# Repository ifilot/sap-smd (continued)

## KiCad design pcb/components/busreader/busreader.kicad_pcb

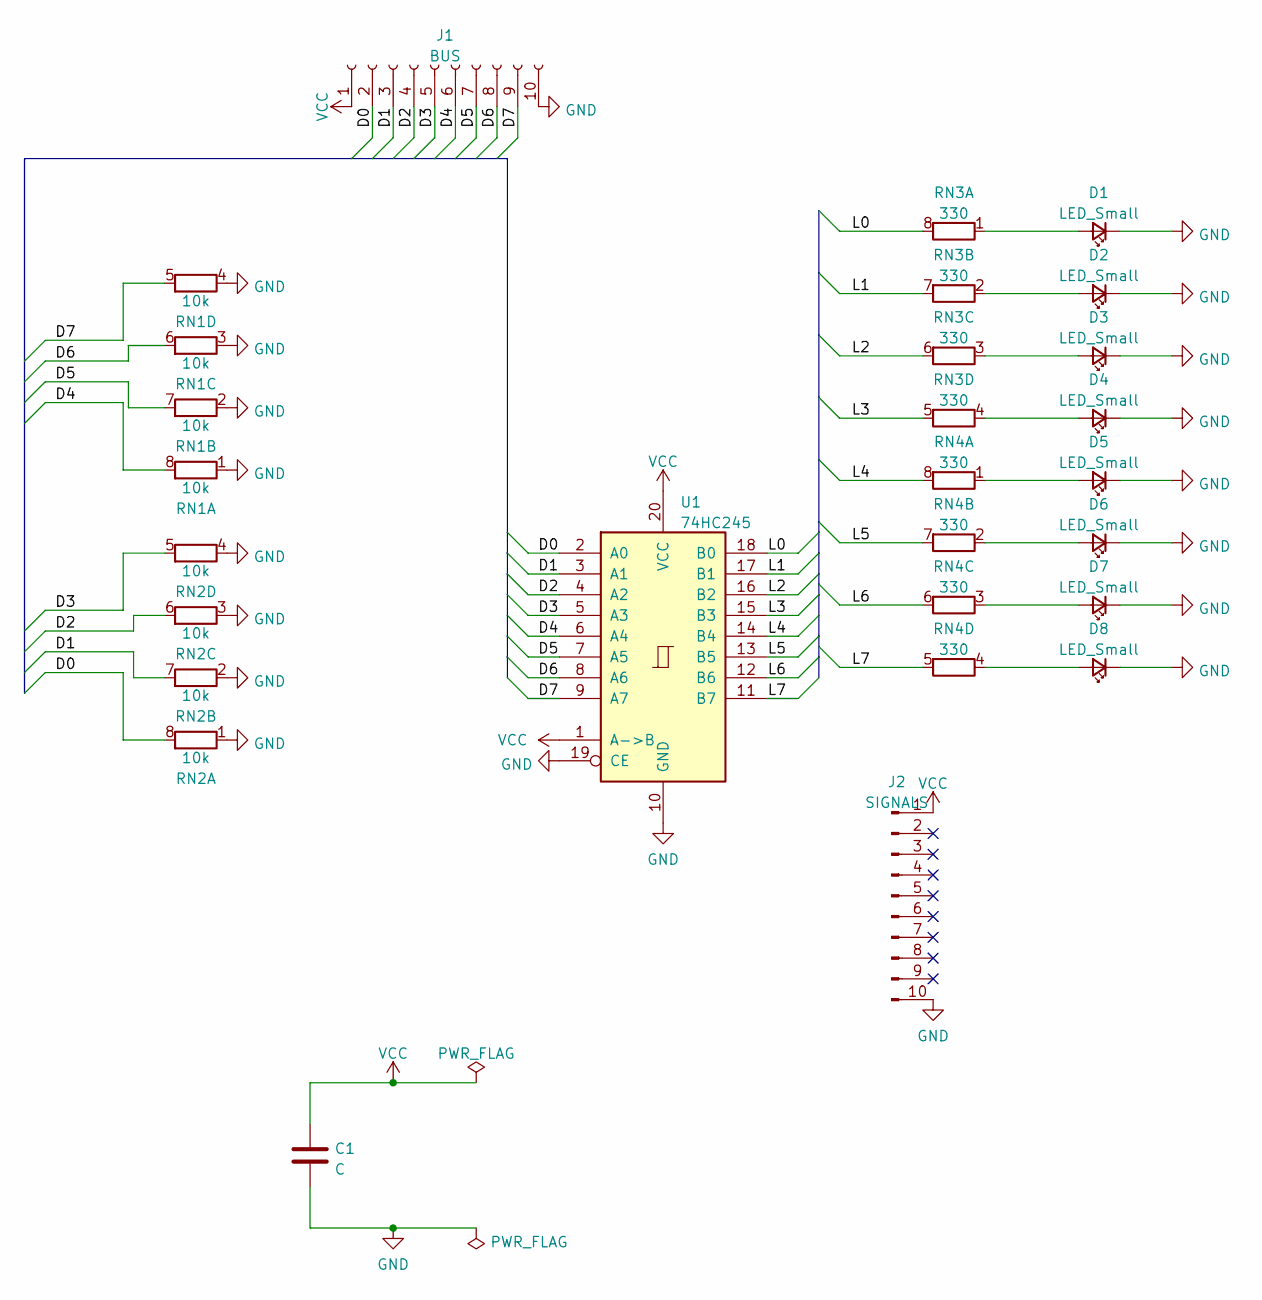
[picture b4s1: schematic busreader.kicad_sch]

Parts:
C1: C; C_0805_2012Metric
D1, D2, D3, D4, D5, D6, D7, D8: LED_Small; LED_0805_2012Metric
J1: BUS; PinHeader_1x10_P2.54mm_Vertical
J2: SIGNALS; PinHeader_1x10_P2.54mm_Vertical
RN1, RN2: 10k; R_Array_Convex_4x0603
RN3, RN4: 330; R_Array_Convex_4x0603
U1: 74HC245; SOIC-20W_7.5x12.8mm_P1.27mm

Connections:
/D0: J1.2, RN2.8 (R1.2), U1.2 (A0)
/D1: J1.3, RN2.7 (R2.2), U1.3 (A1)
/D2: J1.4, RN2.6 (R3.2), U1.4 (A2)
/D3: J1.5, RN2.5 (R4.2), U1.5 (A3)
/D4: J1.6, RN1.8 (R1.2), U1.6 (A4)
/D5: J1.7, RN1.7 (R2.2), U1.7 (A5)
/D6: J1.8, RN1.6 (R3.2), U1.8 (A6)
/D7: J1.9, RN1.5 (R4.2), U1.9 (A7)
/L0: RN3.8 (R1.2), U1.18 (B0)
/L1: RN3.7 (R2.2), U1.17 (B1)
/L2: RN3.6 (R3.2), U1.16 (B2)
/L3: RN3.5 (R4.2), U1.15 (B3)
/L4: RN4.8 (R1.2), U1.14 (B4)
/L5: RN4.7 (R2.2), U1.13 (B5)
/L6: RN4.6 (R3.2), U1.12 (B6)
/L7: RN4.5 (R4.2), U1.11 (B7)
GND: C1.2, D1.1 (K), D2.1 (K), D3.1 (K), D4.1 (K), D5.1 (K), D6.1 (K), D7.1 (K), D8.1 (K), J1.10, J2.10, RN1.1 (R1.1), RN1.2 (R2.1), RN1.3 (R3.1), RN1.4 (R4.1), RN2.1 (R1.1), RN2.2 (R2.1), RN2.3 (R3.1), RN2.4 (R4.1), U1.10 (GND), U1.19 (CE)
unnamed: D1.2 (A), RN3.1 (R1.1)
unnamed: D2.2 (A), RN3.2 (R2.1)
unnamed: D3.2 (A), RN3.3 (R3.1)
unnamed: D4.2 (A), RN3.4 (R4.1)
unnamed: D5.2 (A), RN4.1 (R1.1)
unnamed: D6.2 (A), RN4.2 (R2.1)
unnamed: D7.2 (A), RN4.3 (R3.1)
unnamed: D8.2 (A), RN4.4 (R4.1)
VCC: C1.1, J1.1, J2.1, U1.1 (A->B), U1.20 (VCC)

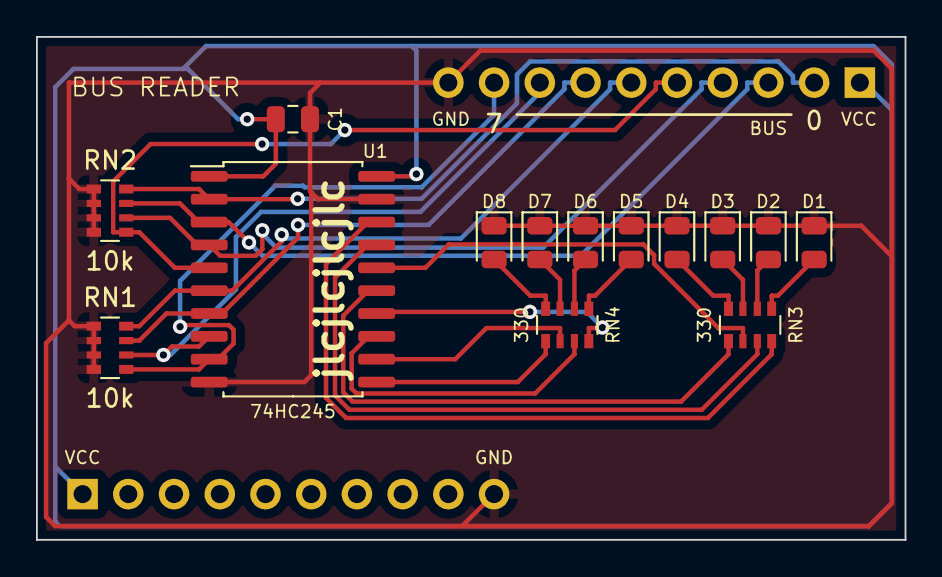
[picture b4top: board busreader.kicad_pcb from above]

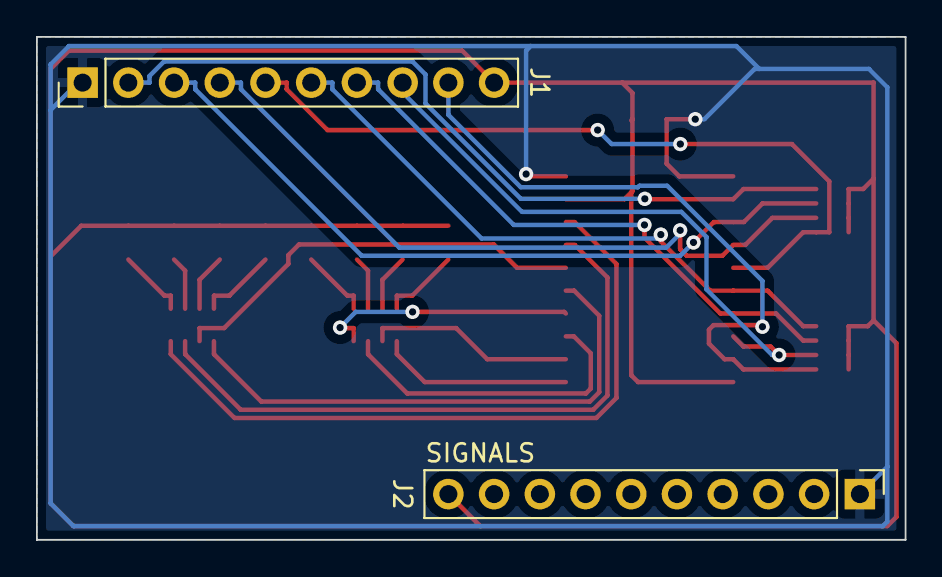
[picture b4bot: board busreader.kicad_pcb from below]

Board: 2 copper layers, 48.3 x 27.9 mm, 16 parts (2 on the bottom side), 26 nets.

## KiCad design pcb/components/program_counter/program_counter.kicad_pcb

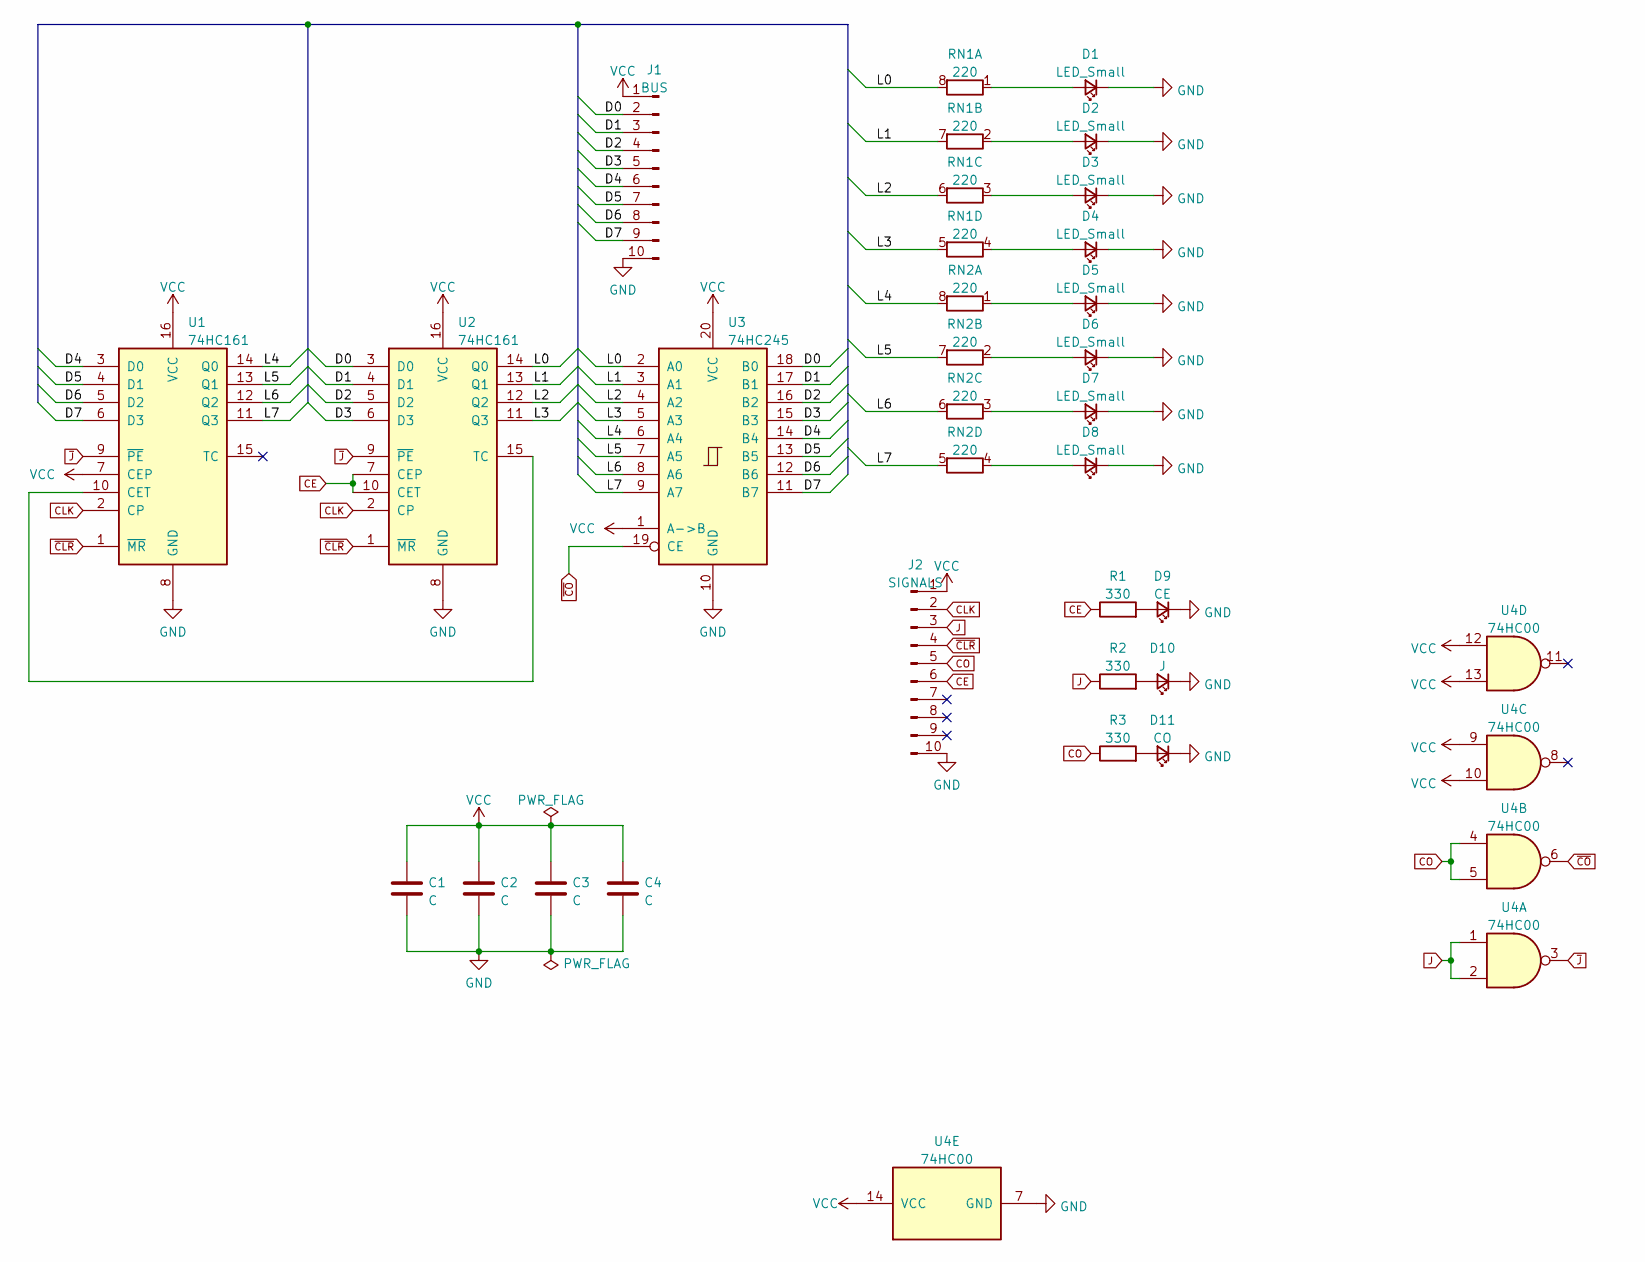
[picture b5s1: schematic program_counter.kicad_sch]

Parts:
C1, C2, C3, C4: C; C_0805_2012Metric
D1, D2, D3, D4, D5, D6, D7, D8: LED_Small; LED_0805_2012Metric
D9: CE; LED_0805_2012Metric
D10: J; LED_0805_2012Metric
D11: CO; LED_0805_2012Metric
J1: BUS; PinHeader_1x10_P2.54mm_Vertical
J2: SIGNALS; PinHeader_1x10_P2.54mm_Vertical
R1, R2, R3: 330; R_0805_2012Metric
RN1, RN2: 220; R_Array_Convex_4x0603
U1, U2: 74HC161; SO-16_3.9x9.9mm_P1.27mm
U3: 74HC245; SOIC-20W_7.5x12.8mm_P1.27mm
U4: 74HC00; SO-14_3.9x8.65mm_P1.27mm

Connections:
/D0: J1.2, U2.3 (D0), U3.18 (B0)
/D1: J1.3, U2.4 (D1), U3.17 (B1)
/D2: J1.4, U2.5 (D2), U3.16 (B2)
/D3: J1.5, U2.6 (D3), U3.15 (B3)
/D4: J1.6, U1.3 (D0), U3.14 (B4)
/D5: J1.7, U1.4 (D1), U3.13 (B5)
/D6: J1.8, U1.5 (D2), U3.12 (B6)
/D7: J1.9, U1.6 (D3), U3.11 (B7)
/L0: RN1.8 (R1.2), U2.14 (Q0), U3.2 (A0)
/L1: RN1.7 (R2.2), U2.13 (Q1), U3.3 (A1)
/L2: RN1.6 (R3.2), U2.12 (Q2), U3.4 (A2)
/L3: RN1.5 (R4.2), U2.11 (Q3), U3.5 (A3)
/L4: RN2.8 (R1.2), U1.14 (Q0), U3.6 (A4)
/L5: RN2.7 (R2.2), U1.13 (Q1), U3.7 (A5)
/L6: RN2.6 (R3.2), U1.12 (Q2), U3.8 (A6)
/L7: RN2.5 (R4.2), U1.11 (Q3), U3.9 (A7)
CE: J2.6, R1.1, U2.7 (CEP), U2.10 (CET)
CLK: J2.2, U1.2 (CP), U2.2 (CP)
CO: J2.5, R3.1, U4.4, U4.5
GND: C1.2, C2.2, C3.2, C4.2, D1.1 (K), D2.1 (K), D3.1 (K), D4.1 (K), D5.1 (K), D6.1 (K), D7.1 (K), D8.1 (K), D9.1 (K), D10.1 (K), D11.1 (K), J1.10, J2.10, U1.8 (GND), U2.8 (GND), U3.10 (GND), U4.7 (GND)
J: J2.3, R2.1, U4.1, U4.2
unnamed: D1.2 (A), RN1.1 (R1.1)
unnamed: D2.2 (A), RN1.2 (R2.1)
unnamed: D3.2 (A), RN1.3 (R3.1)
unnamed: D4.2 (A), RN1.4 (R4.1)
unnamed: D5.2 (A), RN2.1 (R1.1)
unnamed: D6.2 (A), RN2.2 (R2.1)
unnamed: D7.2 (A), RN2.3 (R3.1)
unnamed: D8.2 (A), RN2.4 (R4.1)
unnamed: D9.2 (A), R1.2
unnamed: D10.2 (A), R2.2
unnamed: D11.2 (A), R3.2
unnamed: U1.10 (CET), U2.15 (TC)
VCC: C1.1, C2.1, C3.1, C4.1, J1.1, J2.1, U1.7 (CEP), U1.16 (VCC), U2.16 (VCC), U3.1 (A->B), U3.20 (VCC), U4.9, U4.10, U4.12, U4.13, U4.14 (VCC)
~CLR: J2.4, U1.1 (~MR), U2.1 (~MR)
~CO: U3.19 (CE), U4.6
~J: U1.9 (~PE), U2.9 (~PE), U4.3

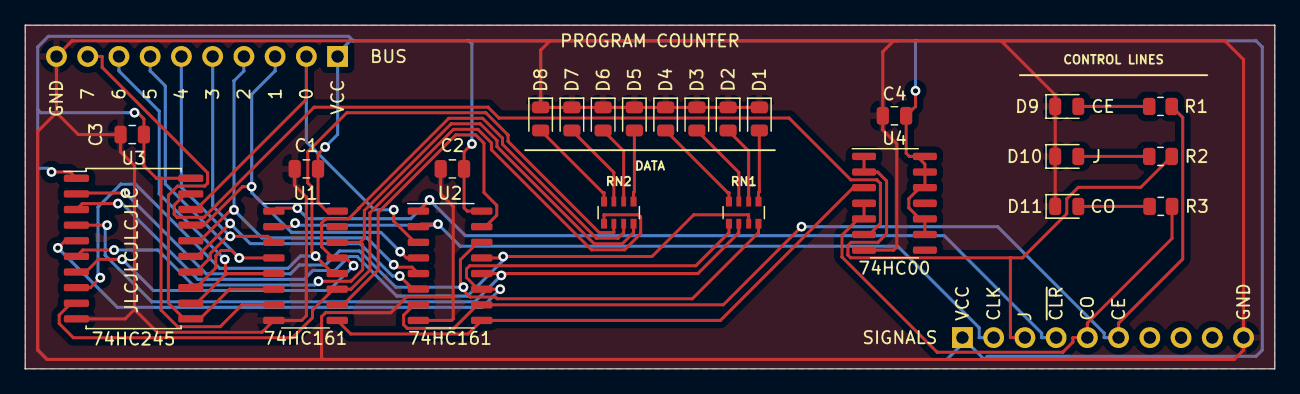
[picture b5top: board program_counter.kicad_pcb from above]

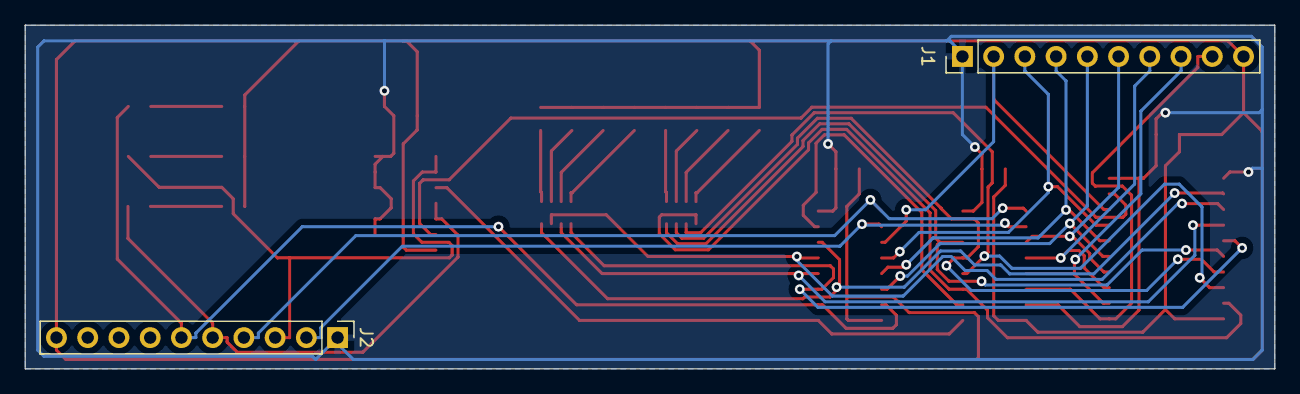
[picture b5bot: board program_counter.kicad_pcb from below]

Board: 2 copper layers, 101.6 x 27.9 mm, 26 parts (2 on the bottom side), 37 nets.

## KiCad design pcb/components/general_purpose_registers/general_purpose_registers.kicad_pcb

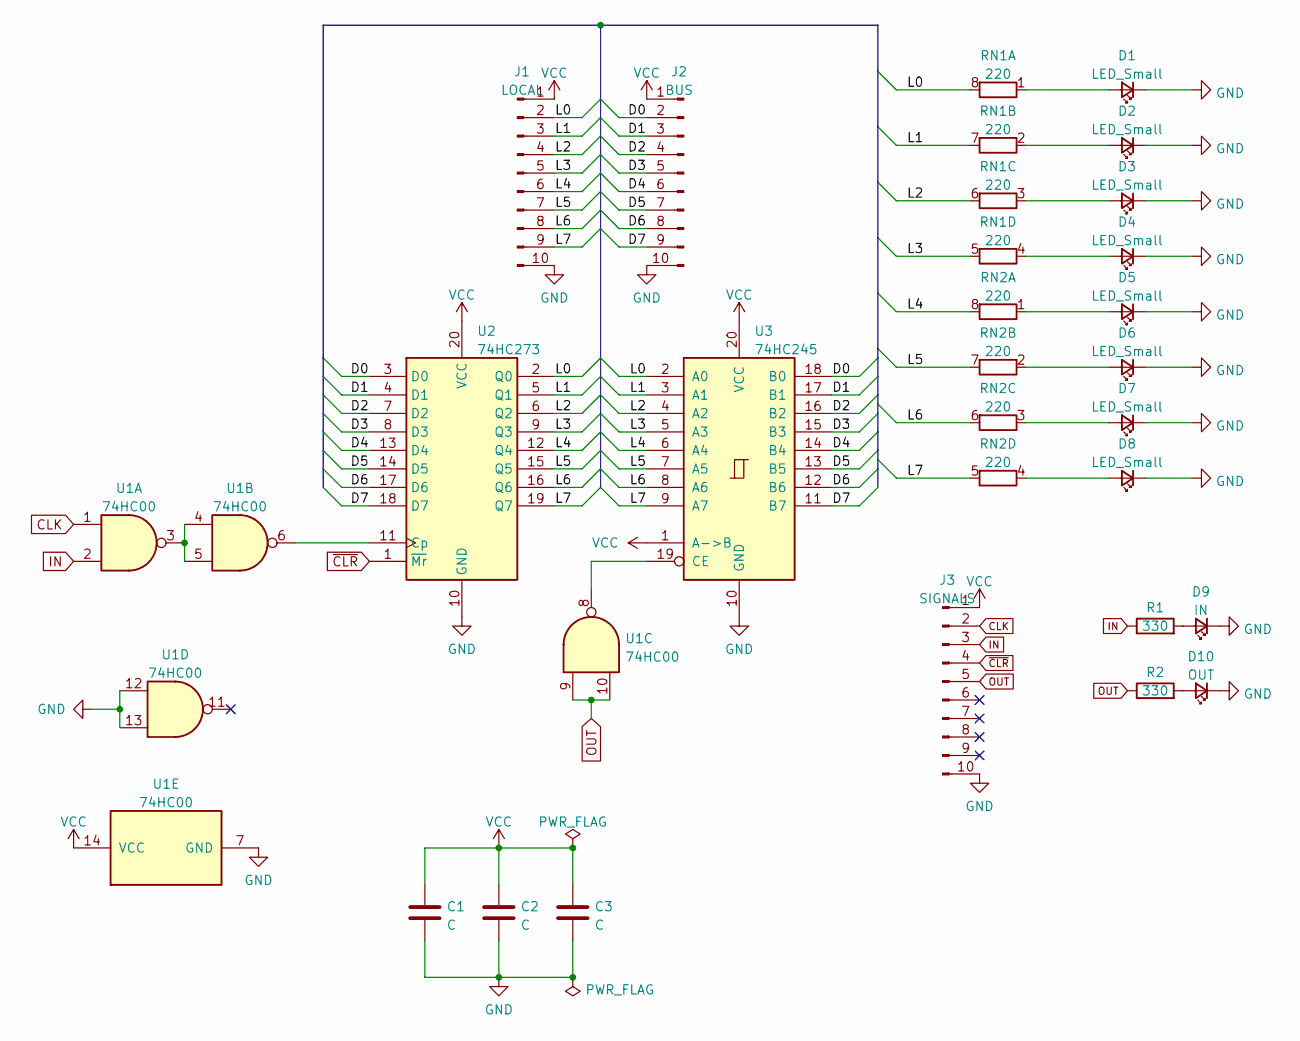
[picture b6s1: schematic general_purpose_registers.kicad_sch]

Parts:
C1, C2, C3: C; C_0805_2012Metric
D1, D2, D3, D4, D5, D6, D7, D8: LED_Small; LED_0805_2012Metric
D9: IN; LED_0805_2012Metric
D10: OUT; LED_0805_2012Metric
J1: LOCAL; PinHeader_1x10_P2.54mm_Vertical
J2: BUS; PinHeader_1x10_P2.54mm_Vertical
J3: SIGNALS; PinHeader_1x10_P2.54mm_Vertical
R1, R2: 330; R_0805_2012Metric
RN1, RN2: 220; R_Array_Convex_4x0603
U1: 74HC00; SO-14_3.9x8.65mm_P1.27mm
U2: 74HC273; SOIC-20W_7.5x12.8mm_P1.27mm
U3: 74HC245; SOIC-20W_7.5x12.8mm_P1.27mm

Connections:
/D0: J2.2, U2.3 (D0), U3.18 (B0)
/D1: J2.3, U2.4 (D1), U3.17 (B1)
/D2: J2.4, U2.7 (D2), U3.16 (B2)
/D3: J2.5, U2.8 (D3), U3.15 (B3)
/D4: J2.6, U2.13 (D4), U3.14 (B4)
/D5: J2.7, U2.14 (D5), U3.13 (B5)
/D6: J2.8, U2.17 (D6), U3.12 (B6)
/D7: J2.9, U2.18 (D7), U3.11 (B7)
/L0: J1.2, RN1.8 (R1.2), U2.2 (Q0), U3.2 (A0)
/L1: J1.3, RN1.7 (R2.2), U2.5 (Q1), U3.3 (A1)
/L2: J1.4, RN1.6 (R3.2), U2.6 (Q2), U3.4 (A2)
/L3: J1.5, RN1.5 (R4.2), U2.9 (Q3), U3.5 (A3)
/L4: J1.6, RN2.8 (R1.2), U2.12 (Q4), U3.6 (A4)
/L5: J1.7, RN2.7 (R2.2), U2.15 (Q5), U3.7 (A5)
/L6: J1.8, RN2.6 (R3.2), U2.16 (Q6), U3.8 (A6)
/L7: J1.9, RN2.5 (R4.2), U2.19 (Q7), U3.9 (A7)
CLK: J3.2, U1.1
GND: C1.2, C2.2, C3.2, D1.1 (K), D2.1 (K), D3.1 (K), D4.1 (K), D5.1 (K), D6.1 (K), D7.1 (K), D8.1 (K), D9.1 (K), D10.1 (K), J1.10, J2.10, J3.10, U1.7 (GND), U1.12, U1.13, U2.10 (GND), U3.10 (GND)
IN: J3.3, R1.1, U1.2
unnamed: D1.2 (A), RN1.1 (R1.1)
unnamed: D2.2 (A), RN1.2 (R2.1)
unnamed: D3.2 (A), RN1.3 (R3.1)
unnamed: D4.2 (A), RN1.4 (R4.1)
unnamed: D5.2 (A), RN2.1 (R1.1)
unnamed: D6.2 (A), RN2.2 (R2.1)
unnamed: D7.2 (A), RN2.3 (R3.1)
unnamed: D8.2 (A), RN2.4 (R4.1)
unnamed: D9.2 (A), R1.2
unnamed: D10.2 (A), R2.2
unnamed: U1.3, U1.4, U1.5
unnamed: U1.6, U2.11 (Cp)
unnamed: U1.8, U3.19 (CE)
OUT: J3.5, R2.1, U1.9, U1.10
VCC: C1.1, C2.1, C3.1, J1.1, J2.1, J3.1, U1.14 (VCC), U2.20 (VCC), U3.1 (A->B), U3.20 (VCC)
~CLR: J3.4, U2.1 (~Mr)

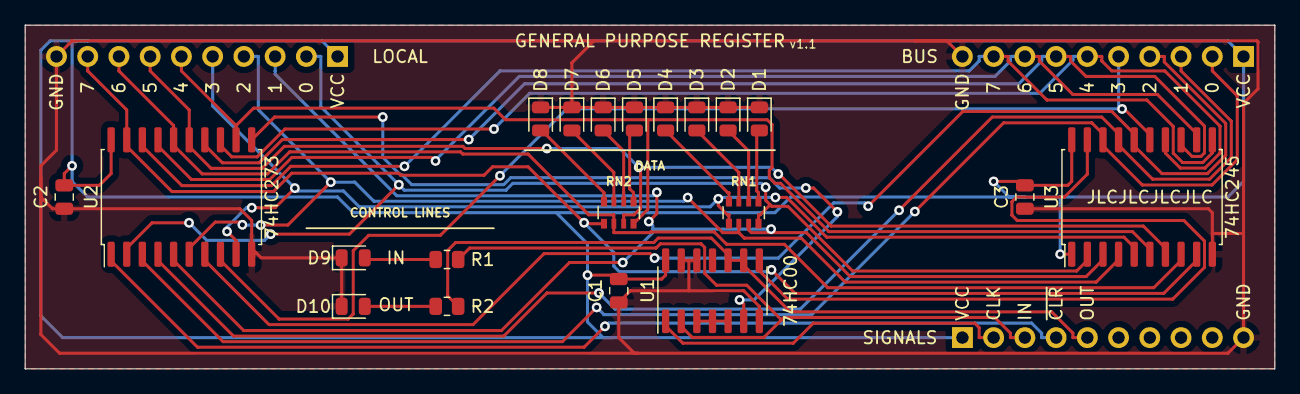
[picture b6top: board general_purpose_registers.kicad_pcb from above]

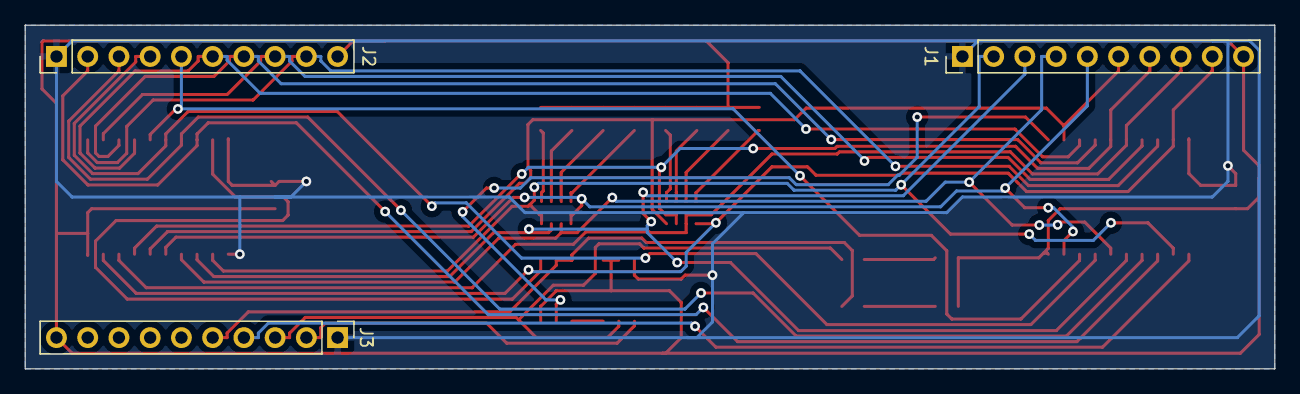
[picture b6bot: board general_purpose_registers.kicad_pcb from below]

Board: 2 copper layers, 101.6 x 27.9 mm, 23 parts (3 on the bottom side), 35 nets.

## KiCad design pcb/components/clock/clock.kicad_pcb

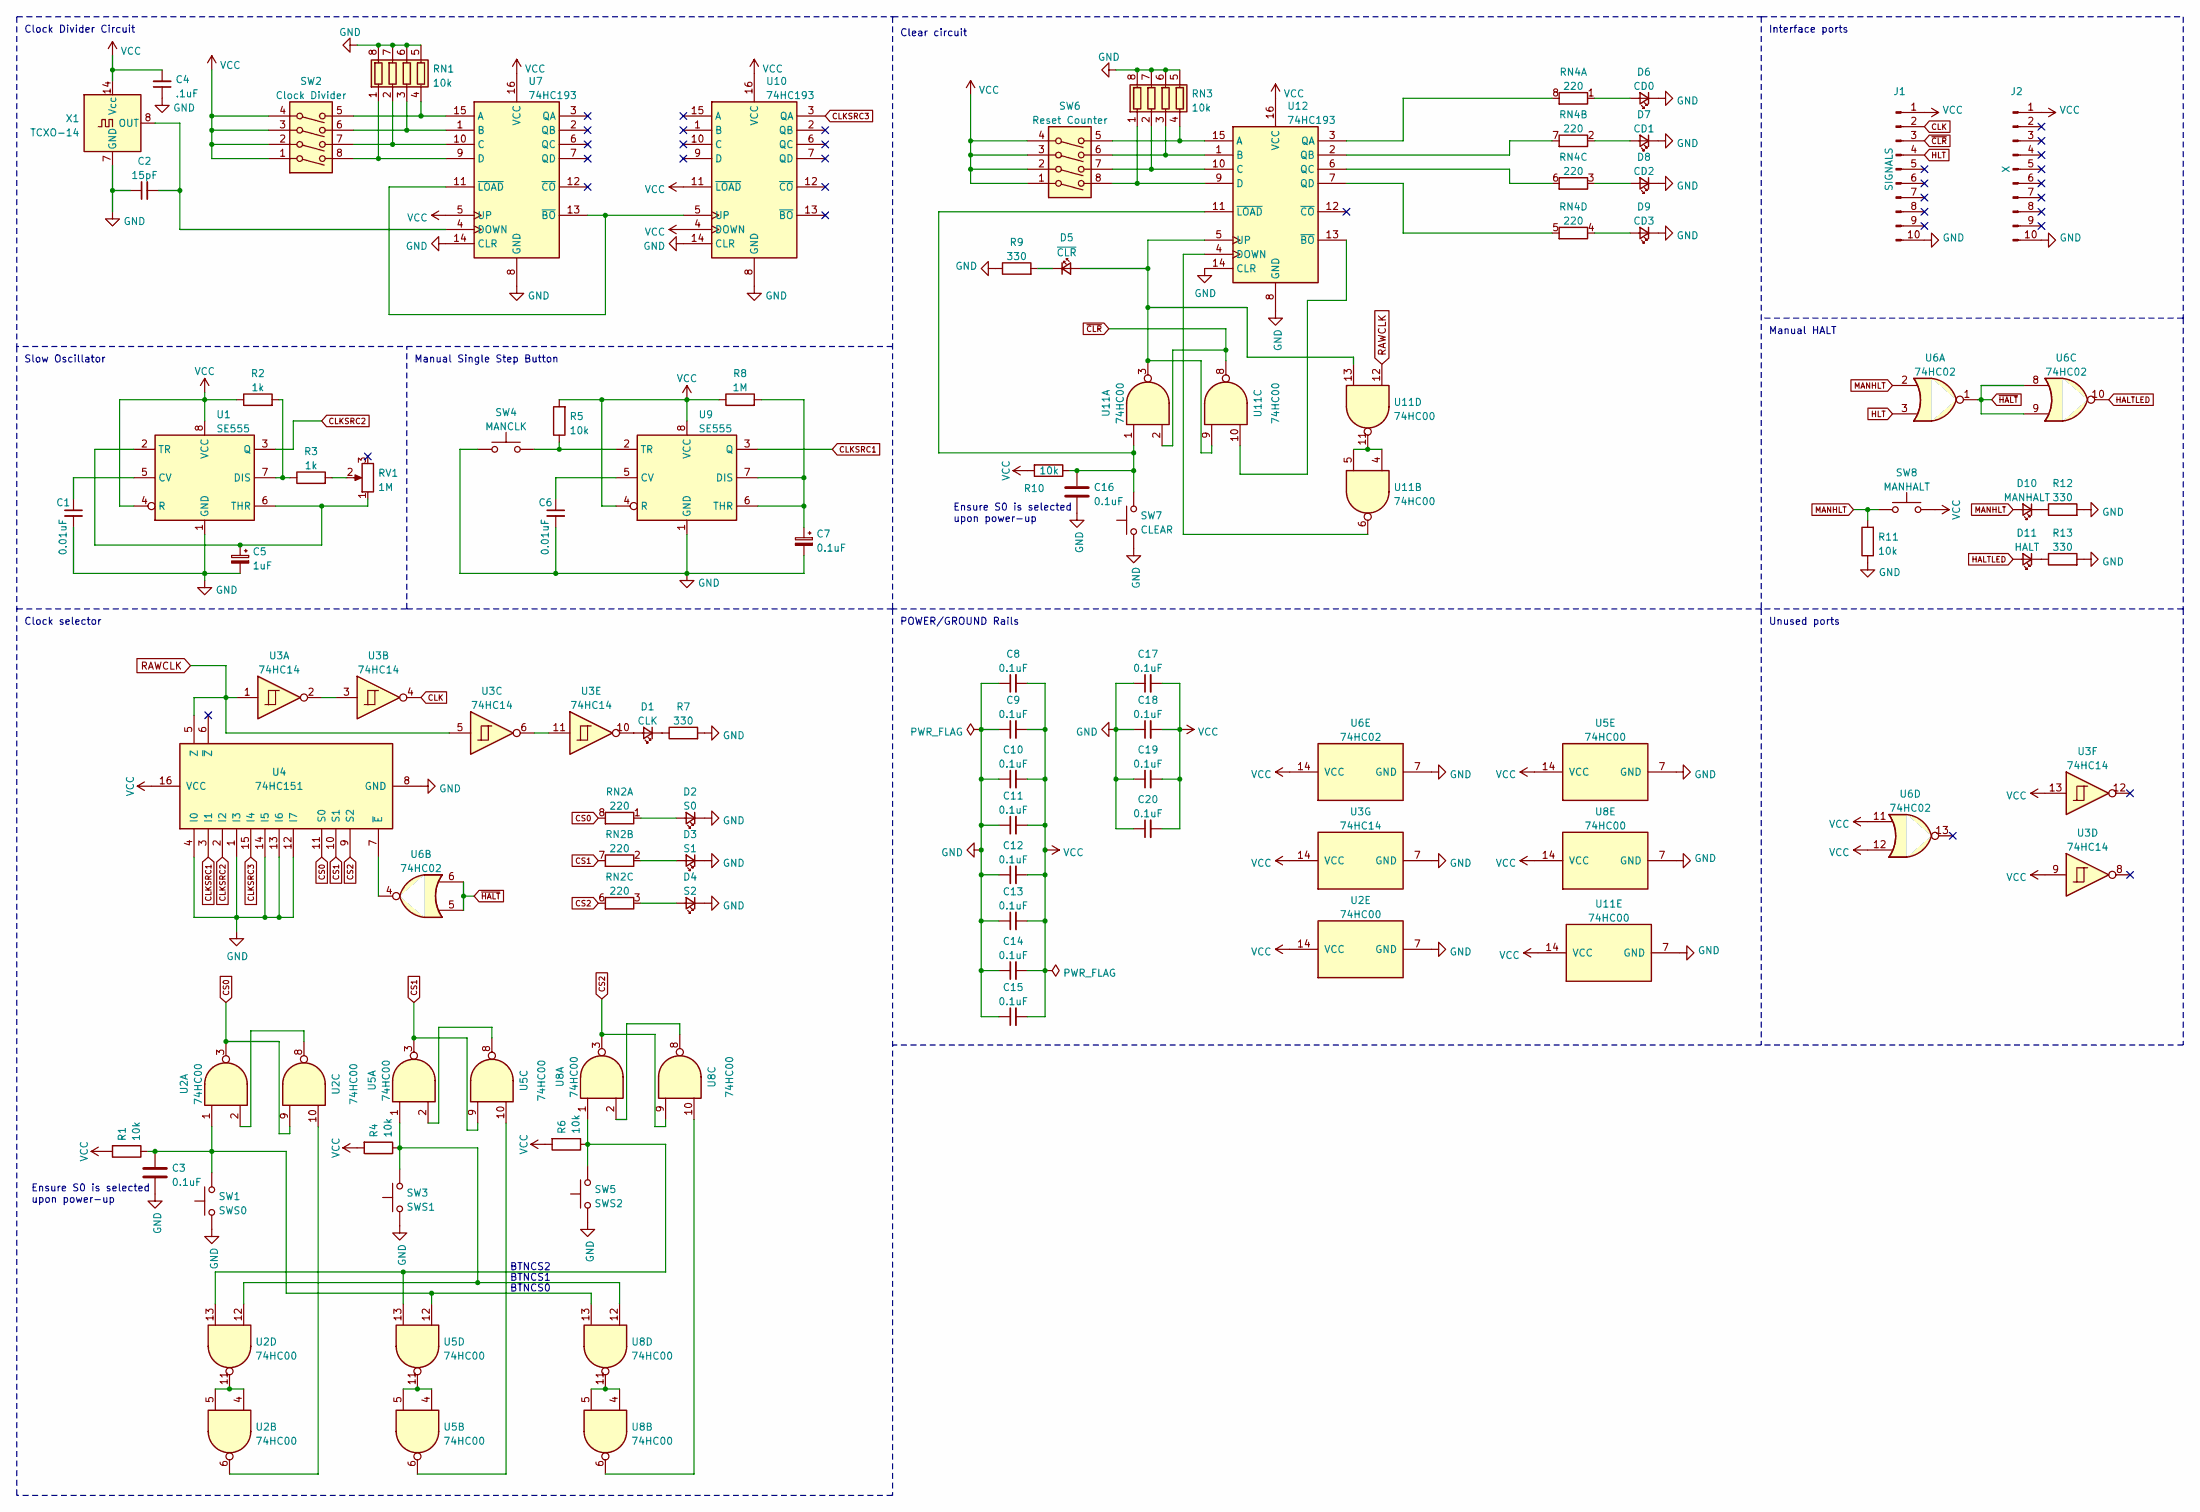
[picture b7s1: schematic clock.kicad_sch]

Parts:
C1, C6: 0.01uF; C_0805_2012Metric_Pad1.18x1.45mm_HandSolder
C2: 15pF; C_0805_2012Metric_Pad1.18x1.45mm_HandSolder
C3, C7, C8, C9, C10, C11, C12, C13, C14, C15, C16, C17, C18, C19, C20: 0.1uF; C_0805_2012Metric_Pad1.18x1.45mm_HandSolder
C4: .1uF; C_0805_2012Metric_Pad1.18x1.45mm_HandSolder
C5: 1uF; C_0805_2012Metric_Pad1.18x1.45mm_HandSolder
D1: CLK; LED_0805_2012Metric_Pad1.15x1.40mm_HandSolder
D2: S0; LED_0805_2012Metric_Pad1.15x1.40mm_HandSolder
D3: S1; LED_0805_2012Metric_Pad1.15x1.40mm_HandSolder
D4: S2; LED_0805_2012Metric_Pad1.15x1.40mm_HandSolder
D5: ~{CLR}; LED_0805_2012Metric_Pad1.15x1.40mm_HandSolder
D6: CD0; LED_0805_2012Metric_Pad1.15x1.40mm_HandSolder
D7: CD1; LED_0805_2012Metric_Pad1.15x1.40mm_HandSolder
D8: CD2; LED_0805_2012Metric_Pad1.15x1.40mm_HandSolder
D9: CD3; LED_0805_2012Metric_Pad1.15x1.40mm_HandSolder
D10: MANHALT; LED_0805_2012Metric_Pad1.15x1.40mm_HandSolder
D11: HALT; LED_0805_2012Metric_Pad1.15x1.40mm_HandSolder
J1: SIGNALS; PinHeader_1x10_P2.54mm_Vertical
J2: X; PinHeader_1x10_P2.54mm_Vertical
R1, R4, R5, R6, R10, R11: 10k; R_0805_2012Metric_Pad1.20x1.40mm_HandSolder
R2, R3: 1k; R_0805_2012Metric_Pad1.20x1.40mm_HandSolder
R7, R9, R12, R13: 330; R_0805_2012Metric_Pad1.20x1.40mm_HandSolder
R8: 1M; R_0805_2012Metric_Pad1.20x1.40mm_HandSolder
RN1, RN3: 10k; R_Array_Convex_4x0603
RN2, RN4: 220; R_Array_Convex_4x0603
RV1: 1M; Potentiometer_ACP_CA9-V10_Vertical
SW1: SWS0; SW_PUSH_6mm
SW2: Clock Divider; SW_DIP_SPSTx04_Slide_6.7x11.72mm_W8.61mm_P2.54mm_LowProfile
SW3: SWS1; SW_PUSH_6mm
SW4: MANCLK; SW_PUSH-12mm_Wuerth-430476085716
SW5: SWS2; SW_PUSH_6mm
SW6: Reset Counter; SW_DIP_SPSTx04_Slide_6.7x11.72mm_W8.61mm_P2.54mm_LowProfile
SW7: CLEAR; SW_PUSH_6mm
SW8: MANHALT; tactile_button
U1, U9: SE555; SOIC-8_3.9x4.9mm_P1.27mm
U2, U5, U8, U11: 74HC00; SO-14_3.9x8.65mm_P1.27mm
U3: 74HC14; SO-14_3.9x8.65mm_P1.27mm
U4: 74HC151; SO-16_3.9x9.9mm_P1.27mm
U6: 74HC02; SO-14_3.9x8.65mm_P1.27mm
U7, U10, U12: 74HC193; SO-16_3.9x9.9mm_P1.27mm
X1: TCXO-14; Oscillator_DIP-14

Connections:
CLK: J1.2, U3.4
CLKSRC1: U4.3 (I1), U9.3 (Q)
CLKSRC2: U1.3 (Q), U4.2 (I2)
CLKSRC3: U4.15 (I4), U10.3 (QA)
CS0: RN2.8 (R1.2), U2.3, U2.9, U4.11 (S0)
CS1: RN2.7 (R2.2), U4.10 (S1), U5.3, U5.9
CS2: RN2.6 (R3.2), U4.9 (S2), U8.3, U8.9
GND: C1.2, C2.1, C3.2, C4.1, C5.2, C6.2, C7.2, C8.1, C9.1, C10.1, C11.1, C12.1, C13.1, C14.1, C15.1, C16.2, C17.1, C18.1, C19.1, C20.1, D2.1 (K), D3.1 (K), D4.1 (K), D6.1 (K), D7.1 (K), D8.1 (K), D9.1 (K), J1.10, J2.10, R7.2, R9.1, R11.1, R12.2, R13.2, RN1.5 (R4.2), RN1.6 (R3.2), RN1.7 (R2.2), RN1.8 (R1.2), RN3.5 (R4.2), RN3.6 (R3.2), RN3.7 (R2.2), RN3.8 (R1.2), SW1.1, SW3.1, SW4.1, SW5.1, SW7.1, U1.1 (GND), U2.7 (GND), U3.7 (GND), U4.1 (I3), U4.4 (I0), U4.8 (GND), U4.12 (I7), U4.13 (I6), U4.14 (I5), U5.7 (GND), U6.7 (GND), U7.8 (GND), U7.14 (CLR), U8.7 (GND), U9.1 (GND), U10.8 (GND), U10.14 (CLR), U11.7 (GND), U12.8 (GND), U12.14 (CLR), X1.7 (GND)
HALTLED: D11.2 (A), U6.10
HLT: J1.4, U6.3
MANHLT: D10.2 (A), R11.2, SW8.1, U6.2
unnamed: C1.1, U1.5 (CV)
unnamed: C2.2, U7.4 (DOWN), X1.8 (OUT)
unnamed: C3.1, R1.1, SW1.2, U2.1, U5.12, U8.13
unnamed: C5.1, RV1.1, U1.2 (TR), U1.6 (THR)
unnamed: C6.1, U9.5 (CV)
unnamed: C7.1, R8.2, U9.6 (THR), U9.7 (DIS)
unnamed: C16.1, R10.1, SW7.2, U11.1, U12.11 (~LOAD)
unnamed: D1.1 (K), R7.1
unnamed: D1.2 (A), U3.10
unnamed: D2.2 (A), RN2.1 (R1.1)
unnamed: D3.2 (A), RN2.2 (R2.1)
unnamed: D4.2 (A), RN2.3 (R3.1)
unnamed: D5.1 (K), R9.2
unnamed: D5.2 (A), U11.3, U11.9, U11.13, U12.5 (UP)
unnamed: D6.2 (A), RN4.1 (R1.1)
unnamed: D7.2 (A), RN4.2 (R2.1)
unnamed: D8.2 (A), RN4.3 (R3.1)
unnamed: D9.2 (A), RN4.4 (R4.1)
unnamed: D10.1 (K), R12.1
unnamed: D11.1 (K), R13.1
unnamed: R2.2, R3.1, U1.7 (DIS)
unnamed: R3.2, RV1.2
unnamed: R4.1, SW3.2, U2.12, U5.1, U8.12
unnamed: R5.1, SW4.2, U9.2 (TR)
unnamed: R6.1, SW5.2, U2.13, U5.13, U8.1
unnamed: RN1.1 (R1.1), SW2.8, U7.9 (D)
unnamed: RN1.2 (R2.1), SW2.7, U7.10 (C)
unnamed: RN1.3 (R3.1), SW2.6, U7.1 (B)
unnamed: RN1.4 (R4.1), SW2.5, U7.15 (A)
unnamed: RN3.1 (R1.1), SW6.8, U12.9 (D)
unnamed: RN3.2 (R2.1), SW6.7, U12.10 (C)
unnamed: RN3.3 (R3.1), SW6.6, U12.1 (B)
unnamed: RN3.4 (R4.1), SW6.5, U12.15 (A)
unnamed: RN4.5 (R4.2), U12.7 (QD)
unnamed: RN4.6 (R3.2), U12.6 (QC)
unnamed: RN4.7 (R2.2), U12.2 (QB)
unnamed: RN4.8 (R1.2), U12.3 (QA)
unnamed: U2.2, U2.8
unnamed: U2.6, U2.10
unnamed: U2.4, U2.5, U2.11
unnamed: U3.2, U3.3
unnamed: U3.6, U3.11
unnamed: U4.7 (~E), U6.4
unnamed: U5.2, U5.8
unnamed: U5.6, U5.10
unnamed: U5.4, U5.5, U5.11
unnamed: U8.2, U8.8
unnamed: U8.6, U8.10
unnamed: U8.4, U8.5, U8.11
unnamed: U7.11 (~LOAD), U7.13 (~BO), U10.5 (UP)
unnamed: U11.6, U12.4 (DOWN)
unnamed: U11.10, U12.13 (~BO)
unnamed: U11.4, U11.5, U11.11
RAWCLK: U3.1, U3.5, U4.5 (Z), U11.12
VCC: C4.2, C8.2, C9.2, C10.2, C11.2, C12.2, C13.2, C14.2, C15.2, C17.2, C18.2, C19.2, C20.2, J1.1, J2.1, R1.2, R2.1, R4.2, R5.2, R6.2, R8.1, R10.2, SW2.1, SW2.2, SW2.3, SW2.4, SW6.1, SW6.2, SW6.3, SW6.4, SW8.2, U1.4 (R), U1.8 (VCC), U2.14 (VCC), U3.9, U3.13, U3.14 (VCC), U4.16 (VCC), U5.14 (VCC), U6.11, U6.12, U6.14 (VCC), U7.5 (UP), U7.16 (VCC), U8.14 (VCC), U9.4 (R), U9.8 (VCC), U10.4 (DOWN), U10.11 (~LOAD), U10.16 (VCC), U11.14 (VCC), U12.16 (VCC), X1.14 (Vcc)
~CLR: J1.3, U11.2, U11.8
~HALT: U6.1, U6.5, U6.6, U6.8, U6.9

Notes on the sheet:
Unused ports
Manual HALT
Ensure S0 is selected upon power-up
Slow Oscillator
Interface ports
POWER/GROUND Rails
BTNCS1
BTNCS2
Clock Divider Circuit
Clock selector
Manual Single Step Button
BTNCS0
Clear circuit

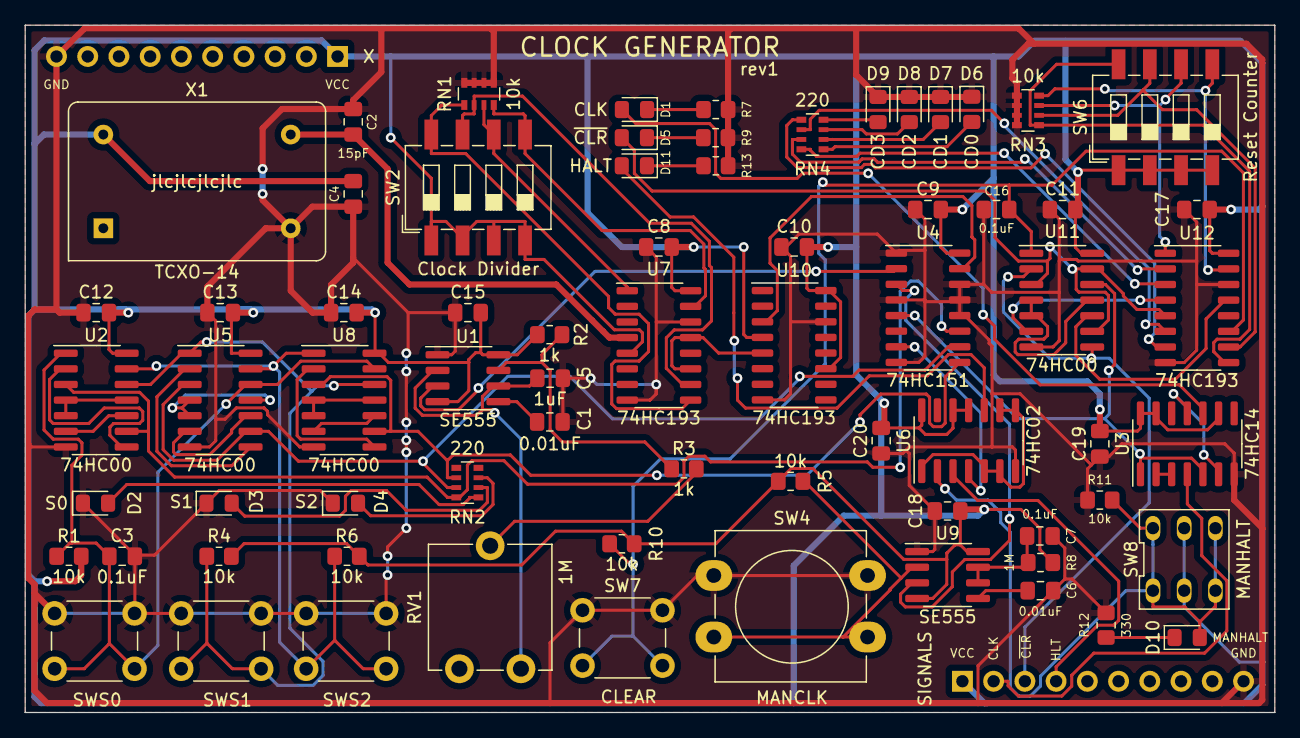
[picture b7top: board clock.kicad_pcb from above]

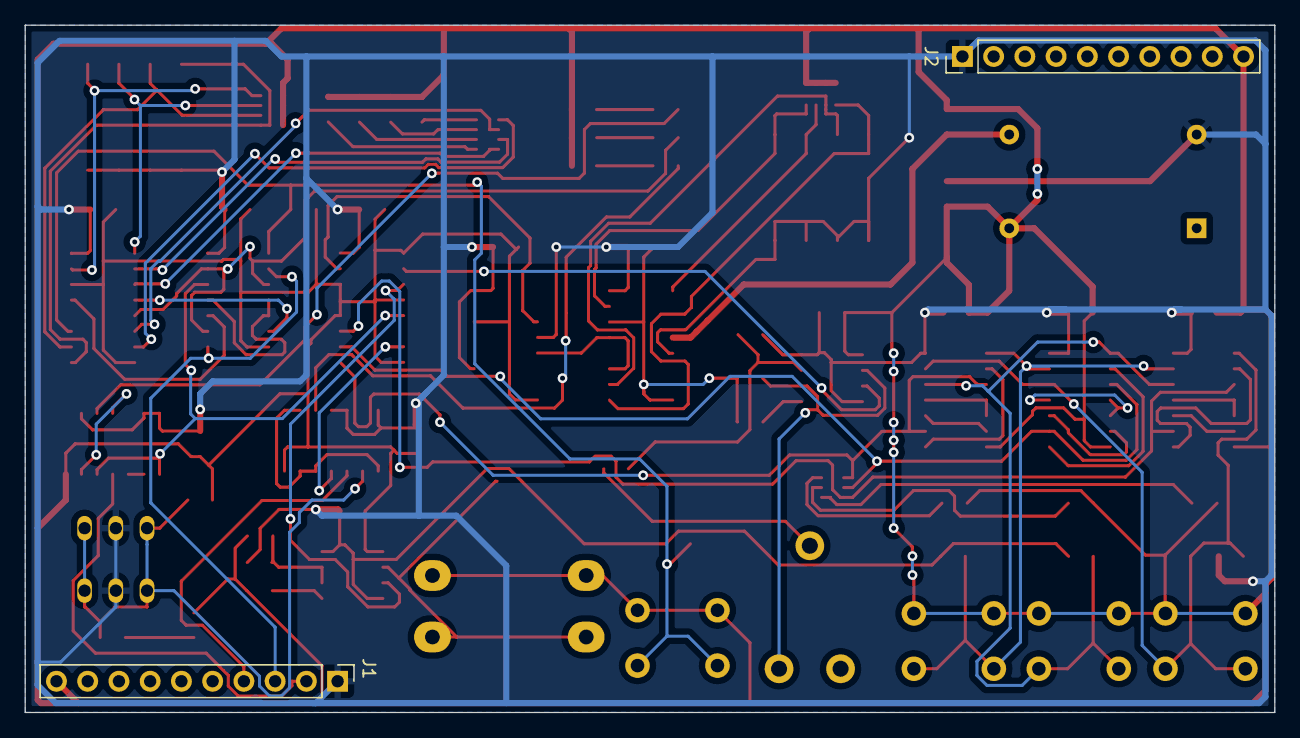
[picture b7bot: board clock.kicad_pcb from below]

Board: 2 copper layers, 101.6 x 55.9 mm, 72 parts (2 on the bottom side), 68 nets.
